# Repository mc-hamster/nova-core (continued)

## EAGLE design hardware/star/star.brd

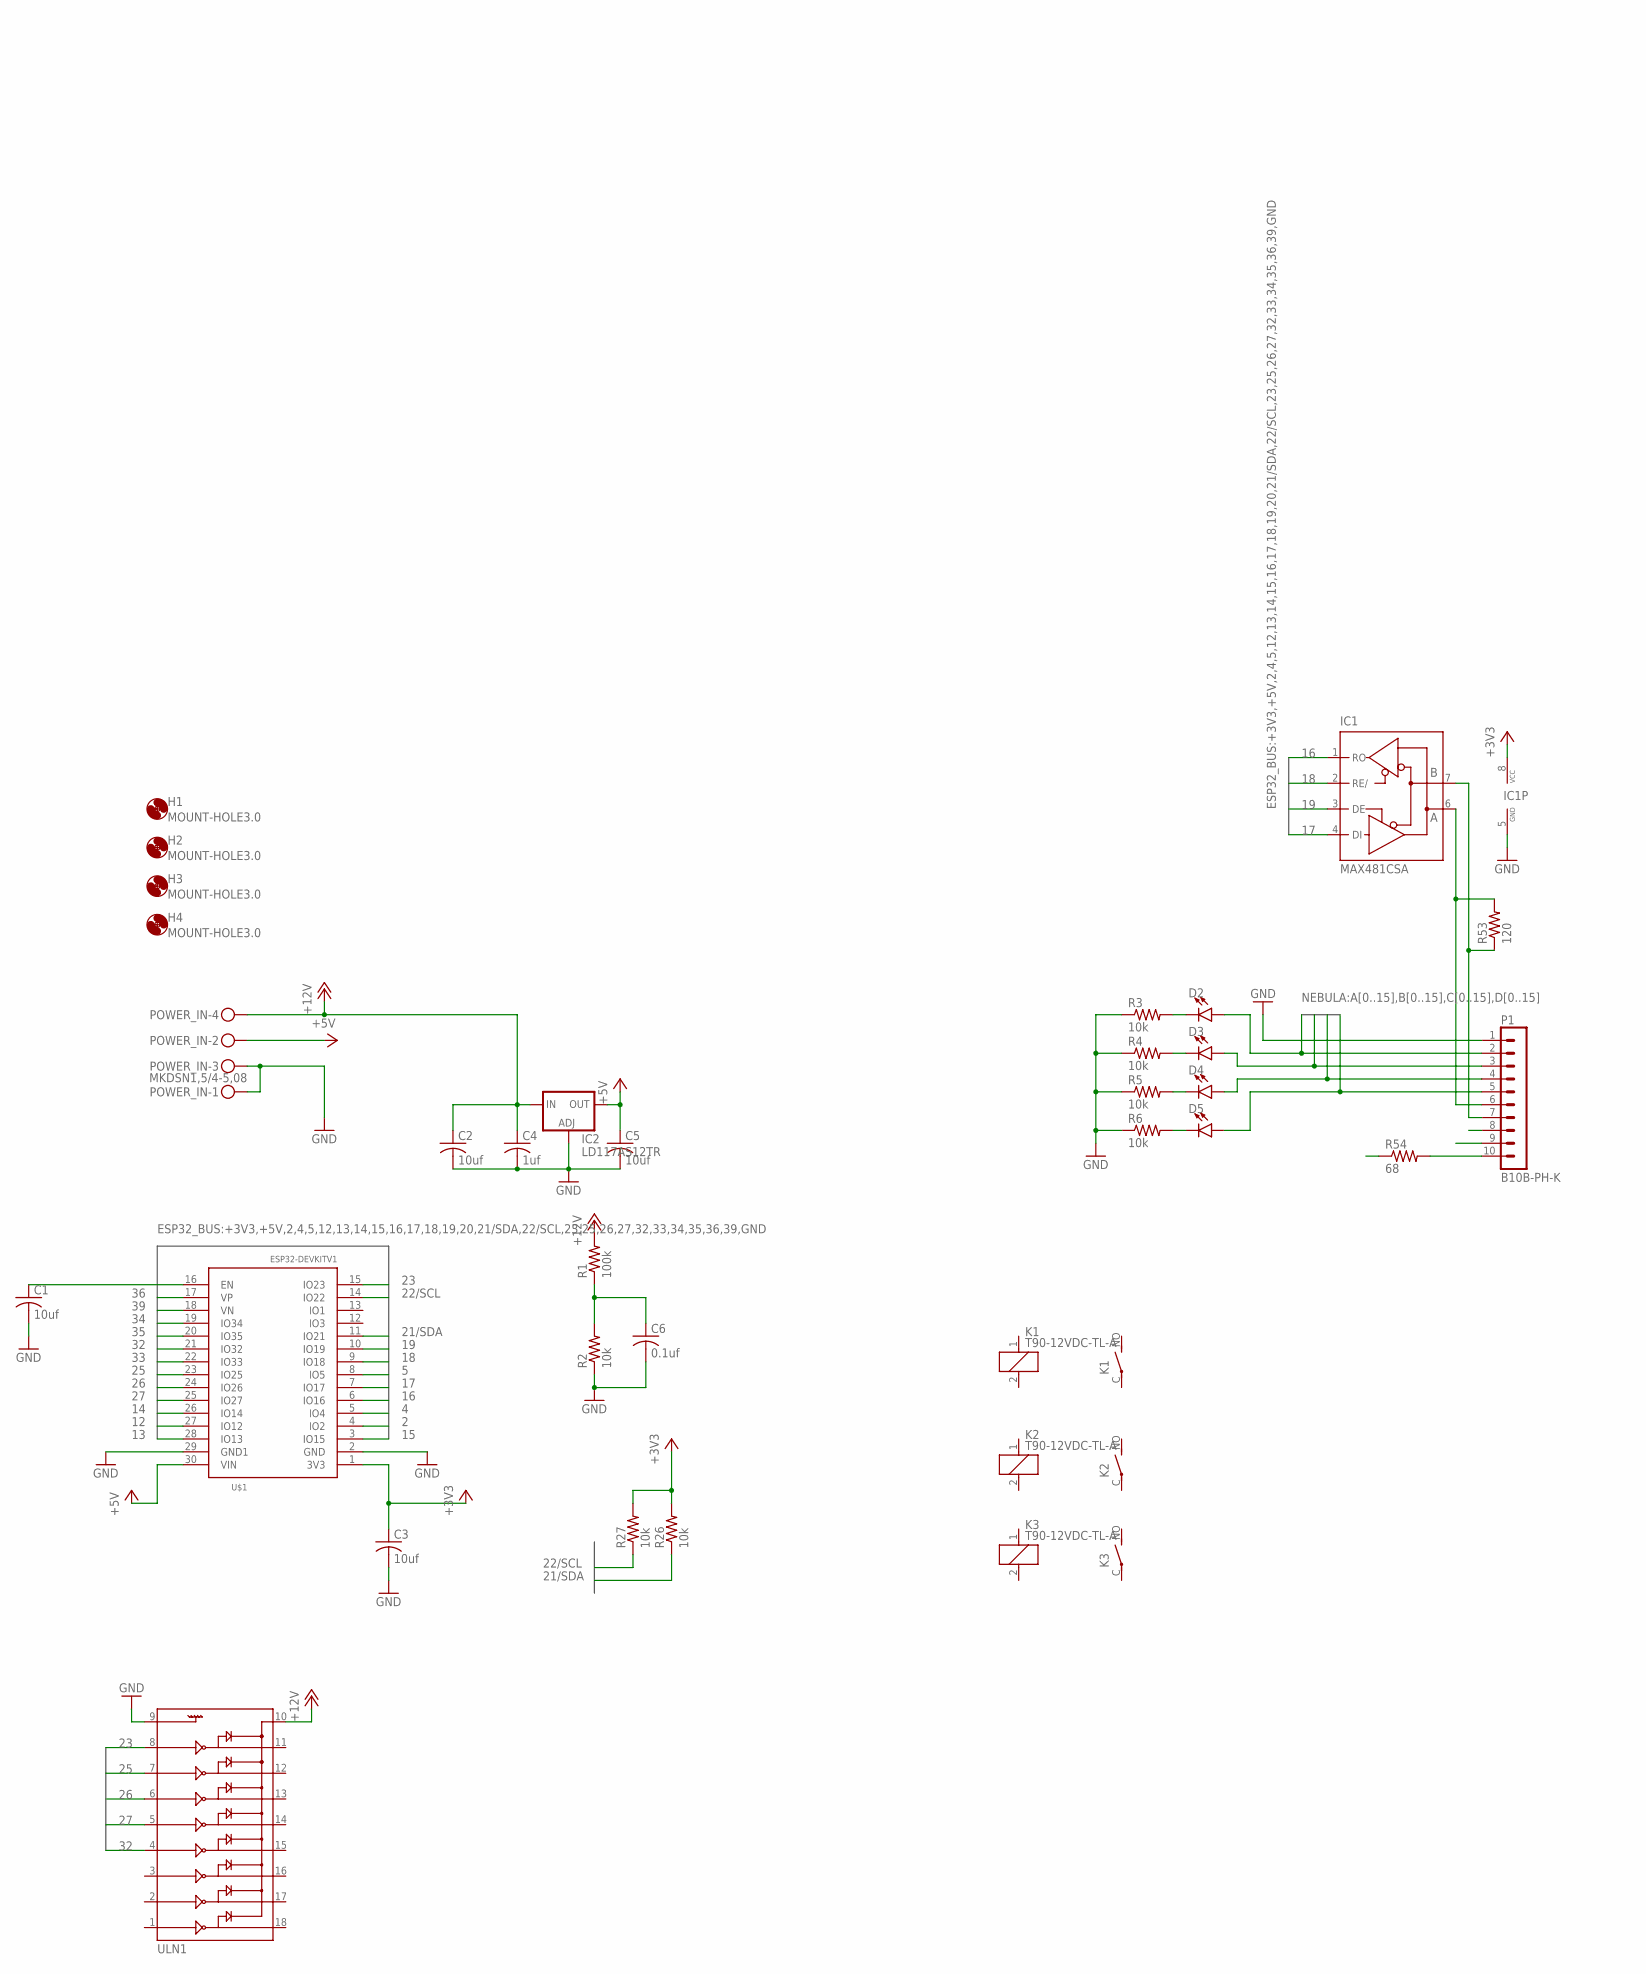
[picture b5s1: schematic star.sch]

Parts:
C1, C2, C3, C5: 10uf; C0603; LCSC_PART_NUMBER C19702
C4: 1uf; C0805; LCSC_PART_NUMBER C15849
C6: 0.1uf; C0603; LCSC_PART_NUMBER C14663
D2, D3, D4, D5: LED0603; LED-0603
H1, H2, H3, H4: MOUNT-HOLE3.0; 3,0
IC1: MAX481CSA; SO08
IC2: LD117AS12TR; SOT223; LCSC_PART_NUMBER C6187
K1, K2, K3: T90-12VDC-TL-A; JT1A-PCB
P1: B10B-PH-K
POWER_IN: MKDSN1,5/4-5,08
R1: 100k; R0603; LCSC_PART_NUMBER C25803
R2, R3, R4, R5, R6, R26, R27: 10k; R0603; LCSC_PART_NUMBER C25804
R53: 120; R0603; LCSC_PART_NUMBER C25804
R54: 68; R0603; LCSC_PART_NUMBER C25804
U$1: ESP32DEVKITV1; ESP32-DEVKITV1
ULN1: ULN2803SOIC; SO018

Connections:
2: U$1.4 (IO2)
4: U$1.5 (IO4)
5: U$1.8 (IO5)
12: U$1.27 (IO12)
13: U$1.28 (IO13)
14: U$1.26 (IO14)
15: U$1.3 (IO15)
16: IC1.1 (RO), U$1.6 (IO16)
17: IC1.4 (DI), U$1.7 (IO17)
18: IC1.2 (RE/), U$1.9 (IO18)
19: IC1.3 (DE), U$1.10 (IO19)
21/SDA: R26.1, U$1.11 (IO21)
22/SCL: R27.1, U$1.14 (IO22)
23: U$1.15 (IO23), ULN1.8
25: U$1.23 (IO25), ULN1.7
26: U$1.24 (IO26), ULN1.6
27: U$1.25 (IO27), ULN1.5
32: U$1.21 (IO32), ULN1.4
33: U$1.22 (IO33)
34: U$1.19 (IO34)
35: U$1.20 (IO35)
36: U$1.17 (VP)
39: C6.1, R1.1, R2.2, U$1.18 (VN)
+3V3: C3.1, IC1.8 (VCC), R26.2, R27.2, U$1.1 (3V3)
+5V: C5.1, IC2.4 (OUT), POWER_IN.2, U$1.30 (VIN)
+12V: C2.1, C4.1, IC2.3 (IN), POWER_IN.4, R1.2, ULN1.10
A0: D2.A, P1.2
A1: D3.A, P1.3
A2: D4.A, P1.4
A3: D5.A, P1.5
GND: C1.2, C2.2, C3.2, C4.2, C5.2, C6.2, IC1.5 (GND), IC2.1 (ADJ), P1.1, POWER_IN.1, POWER_IN.3, R2.1, R3.1, R4.1, R5.1, R6.1, U$1.2 (GND), U$1.29 (GND1), ULN1.9
unnamed: C1.1, U$1.16 (EN)
unnamed: D2.C, R3.2
unnamed: D3.C, R4.2
unnamed: D4.C, R5.2
unnamed: D5.C, R6.2
unnamed: P1.10, R54.2
unnamed: IC1.6 (A), P1.6, R53.2
unnamed: IC1.7 (B), P1.7, R53.1

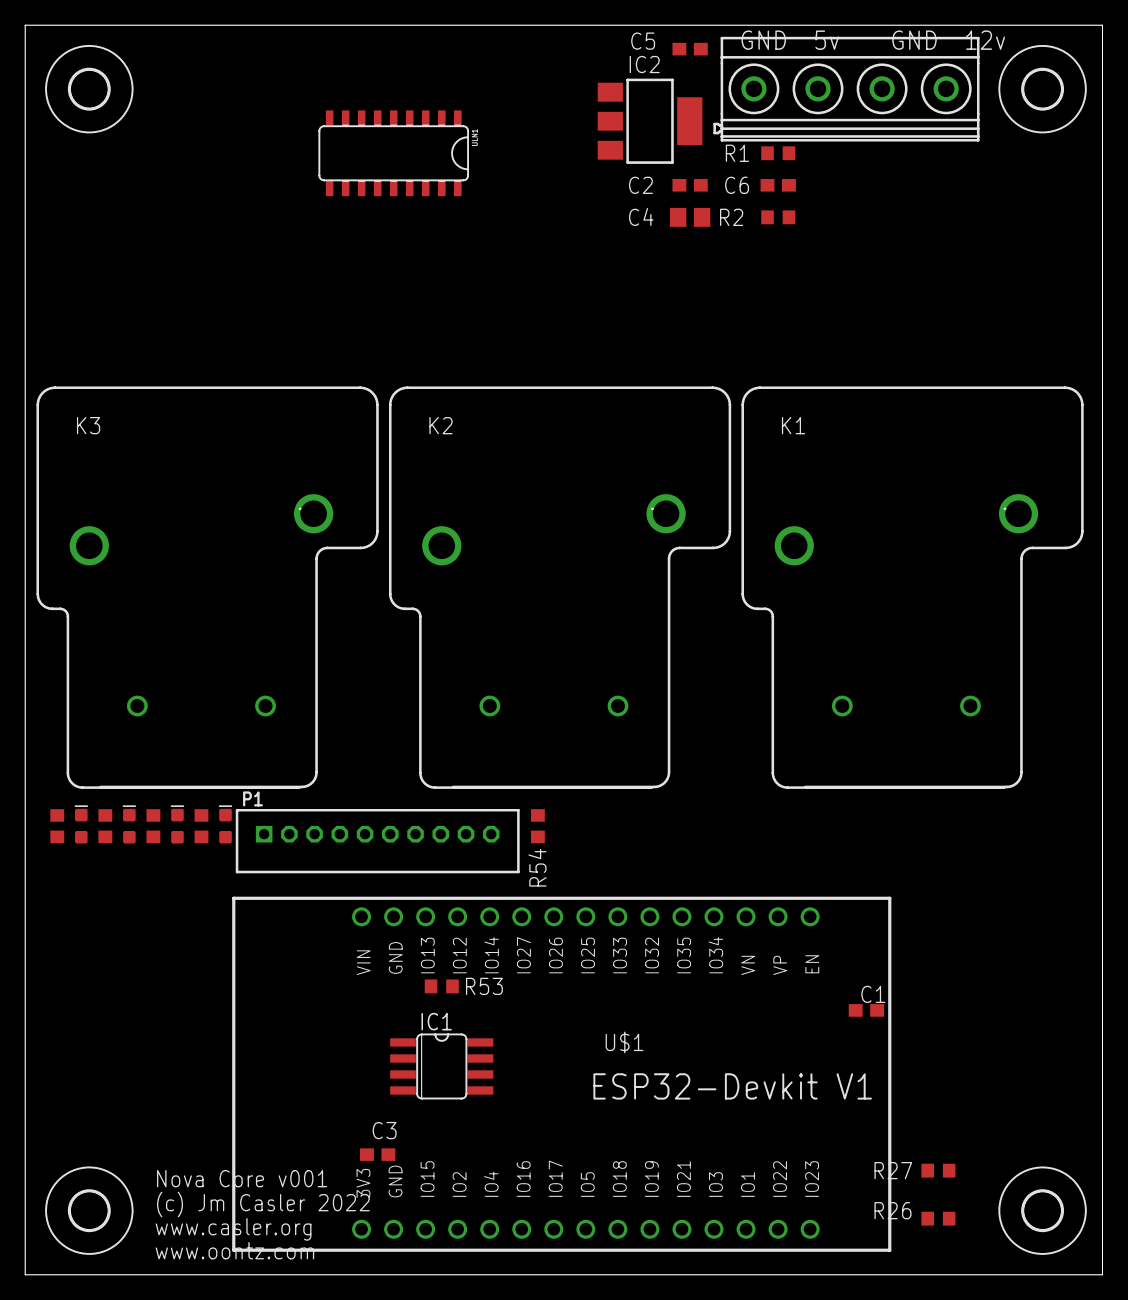
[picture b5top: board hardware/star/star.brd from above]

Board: 4 copper layers, 85.4 x 99.0 mm, 33 parts (0 on the bottom side), 28 nets.

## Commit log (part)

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2022-10-07 Initial checkin
2022-10-07 update schematic
2022-10-11 Core 001 Complete
2022-10-21 build out
2022-10-21 add async webserver example
2022-10-27 add MCP23X17 lib and code
2022-11-27 Nova 3.0 in progress. Needs line drivers.
2022-12-08 start of adding ULN to the outputs
2022-12-16 More Progress
2022-12-19 Completed v3
2022-12-23 Nova Core v3 - Sent to JLC PCB
2023-01-04 Fix for button status resistors & 12v status dim
    Fix for button status resistors & 12v status dim
2023-01-04 updated version number
2023-01-04 updated sample code using adafruit library
2023-01-21 Fixes interrupt on the "H" expander
2023-01-21 Initial work on class for read/write on gpio expander.
2023-01-21 Update boards to remove interrupt for all but expansion H
    Update boards to remove interrupt for all but expansion H
2023-01-22 Switch to FreeRTOS and using semaphores
2023-01-22 wrapper around writeGPIOAB to make it thread safe
2023-01-28 Added poofers, tank manifold and primary fuel shutoff.
2023-02-01 Update phoenix connectors & add JLC_ROTATION
2023-02-01 Replaced output resistor with 68 ohm (part c27592)
2023-02-02 espansion ports
2023-02-16 Add TVS and change led resistors to 1k
2023-02-16 misc board updates
2023-02-16 add midi v1.1 specification
2023-02-17 manual routing complete
2023-02-17 routed
2023-02-18 Updated labels
2023-02-24 v04 complete
2023-03-28 New methods to control button lights and emergenecy stop
2023-04-09 Add labels 5v and 3v3
2023-04-09 Rename src/Simona.cpp to src/modes/Simona.cpp
2023-04-09 Rename src/Simona.h to src/modes/Simona.h
2023-04-09 define output devices, first a star
2023-04-11 Abstract the digitalWrite methods to make them threadsafe
2023-04-11 buttons setup to have click, double and long press
2023-04-11 add more delay. this will give priority to other tasks
2023-04-12 buttons work to control the poofer
2023-04-16 multi-poof almost works
2023-04-21 Fix bug with stop getting in the way of the button lights
2023-04-22 start of boomer and longer running multi poofer
2023-04-25 it all works! fugly as heck but it works.
2023-04-25 add more output to serial console to help debugging
2023-04-25 cleanup serial console
2023-04-28 When button is pushed, blink the light associated with the button.
2023-05-04 New abstraction for port expanders. Use for go poof
2023-05-04 Fix watchdog timeout on system disable
2023-05-04 Set exhaust of boom to 4000ms
2023-05-05 Remap outputs for unscruz.
    I need to fix the cable pigtails. FMYL!
2023-05-06 Reduce button push timeout
2023-05-14 add esp32-s3
    (for future use)
2023-05-17 Reduce duration of poofer output
2023-05-17 Operate loops with smaller timings
2023-05-30 Tighter timing.
2023-05-30 Update loop delays in button thread
    This will improve UE when system is enabled and give priority to other threads when the system is disabled.
2023-05-30 Begin the use of jtag
2023-05-30 Task Ambient is now Task Enable
2023-05-30 Describe the class
2023-06-04 Move ESPUI to web
2023-06-04 Add ESPUI and ASyncTCP
2023-06-04 Improve responsiveness
2023-06-04 persistance to json
2023-06-15 add proto for the messaging request/response
2023-06-15 web interface
2023-06-19 no compile errors!
2023-06-19 fix compiler warning
2023-06-19 adding ReqRes. May end up removing this
2023-06-20 remove ReqRes
2023-06-20 make novaio easier to read
2023-06-30 Messages are now sent over the serial interface!
2023-07-02 stashing the v2 board with the new processor. likely not going to be used.
2023-07-02 re & de status LEDs added
2023-07-02 add definitions for the remaining outputs
2023-07-05 Add yields to Ambient
2023-07-07 Datasheet for the rs485 transceiver we use
2023-07-07 make crc16_ccitt easier to read
2023-07-07 monitor stack
2023-07-07 add mcp_h.pinMode
2023-07-07 Initial check in of LightUtils.
2023-07-08 Web interface controls lighting
2023-07-09 Control of lights over web interface works
2023-07-13 I2C clock to 400k & append mac to wifi AP
2023-07-13 add resetConfigSwitch and resetRebootSwitch
2023-07-13 Move xBlockTime to a precompiler define
2023-07-13 frames are being transmitted
2023-07-18 Fixed mapping of light fixgtures to the outputs.
2023-07-18 Continue program operation when returning
2023-07-18 Add the white_dot
2023-07-18 Refactor memory allocations
2023-07-18 Add whitedot and the other colors
2023-07-18 Reduce stack space and modify how often tasks run
2023-07-18 remove digitalWrite, it's not used and dangerous
2023-07-18 New "manual" tab
2023-07-18 cleanup and rename pooferInterval to pooferDuration
2023-07-19 Tune the tasks
2023-07-20 More tuning of the tasks
2023-07-20 Game works with the poofers!
2023-07-20 Clarified which frame average is reported
2023-07-20 Beginning of Boom sequences
    Beginning of Boom sequences
2023-07-23 Fix Pre & Post DMX mapping
2023-07-23 decrease frequency of free stack size reporting
2023-07-23 MVP! MVP! MVP!
2023-07-23 cleanup print statements in task loops
2023-07-24 Fix typo
2023-07-24 I think this done enough
2023-07-24 add documentation
2023-07-27 complete work on fog machines
2023-07-27 send Amnesia more reliably
2023-08-05 Exception decoded, copied from meshtastic
2023-08-05 automatic sequences
2023-08-05 add active feedback on button pushes
2023-08-06 add 500ms more fuel
2023-08-10 speed up brightness fade
2023-08-10 Remove settings tab
2023-08-12 Fix bug in init of bug 13->20
2023-08-12 New StarSequence library
2023-08-18 forgot to check this in
2023-08-27 3 more seconds of exhaust
2023-08-27 Simplify the game
2023-09-03 skip boom on star 6 (zero indexed)
2024-12-27 Update platformio.ini
    Updated to new espressif32 and littlefs
2025-03-02 combine nova star and nova core
2025-03-02 Remove unused variables.
2025-03-06 remove unused modes
2025-03-06 update comment
2025-03-06 reduce cpu load
2025-03-07 move buttons into modes
2025-03-07 initial integration of simona
2025-03-09 Upgrade libraries
2025-03-09 Simona is now fully ported to Nova
2025-03-09 Fix configurations
2025-03-09 Update colors
2025-03-10 Tidy up the console
2025-03-10 Clean up race condition
2025-03-10 Remove TaskButtons
2025-03-10 Remove task buttons
2025-03-10 fix web server heap crash
2025-03-10 The start of virtual stars
2025-03-10 make mutex a little safer
2025-03-10 Cache expansionDigitalRead reads to free up i2c bus
2025-03-10 Add i2c bus utilization
2025-03-11 Fix brightness not loading at startup
2025-03-12 task monitor
2025-03-12 first pass at novanow
2025-03-12 fix bug in rmt
2025-03-13 Update led <-> star <-> dmx map
2025-03-13 reverse second row
2025-03-13 "circular" mode
2025-03-13 added animations
2025-03-14 led animation porting complete
2025-03-14 change max rounds to 12
2025-03-15 reduce button flashing
2025-03-15 better but still broken
2025-03-16 shortened the music
2025-03-16 fixed random number generator
2025-03-16 comment out the goPoof serial print
2025-03-16 boomers are integrated
2025-03-16 suspend gametask and novanow on emergency
2025-03-16 add win animation
2025-03-16 fix prefernce name space error
2025-03-16 Refactoring to make it easier to read
2025-03-16 Revert "Refactoring to make it easier to read"
    This reverts commit 1a2426aa00bba131db1edb5a4b0cce5537a63259.
2025-03-17 Improve performance of TaskStars
2025-03-17 Config for disable debug messages in stars.cpp
2025-03-17 upgrade libs
2025-03-17 update blower off
2025-03-17 add yield
2025-03-17 fix local echo
2025-03-17 fix timing of stars
2025-03-17 wifimulti
2025-03-18 Revert "Fix stalled tasks"
    This reverts commit 07517c7216bb89cdf079c6cdaf90f9eb23ba0c11.
2025-03-18 Revert "Create wifi_config.h"
    This reverts commit 89ce5e07fefa8dec5ebfdf949daa17e2fff7a561.
2025-03-19 fix compiler errors
2025-03-19 fix stalling condition (non critical)
2025-03-19 Update monitoring
2025-03-19 Fix formatting and add startup music
2025-03-20 Update protocol with fogEnabled
2025-03-20 Revert "Update Tasks.cpp"
    This reverts commit a6069fd257d096d91a2489869f4efc050a34c41c.
2025-03-20 update star with fog enable proto
2025-03-20 Refactor NovaNet, NovaIO and FogMachine
2025-03-21 Remove all star, add fogEnabled
2025-03-21 Fix STA status bug, start to add Fog control
2025-03-21 remove fake circular lighting
2025-03-21 fix brightness on startup
2025-03-21 remove mdns
2025-03-21 remove captive portal
2025-03-21 stability improvements
2025-03-22 debouncing
2025-03-22 Updated libs
2025-03-25 Emergency = Turn off Fog Machines
2025-03-26 pass fog messages
2025-03-26 end point works! not yet tested
2025-03-26 update sequences
2025-03-31 add screen and endpoin
2025-04-01 Updates to screen
2025-04-08 Fix xSemaphoreTake bug in NovaIO
2025-04-08 bump priority to 3
2025-04-08 reformat
2025-04-10 Add more loggint to IO
2025-04-10 Switch to case statement
2025-04-10 Bump I2C speed
2025-04-10 i2c reporting
2025-04-23 begin implementation of sensors on nova star
2025-06-09 Fix crash on web update. Caused by update status message
2025-06-10 wrap midi messages in mutex
2025-07-19 Removed web loop mutex
2025-07-19 lightutils format
2025-07-19 Increase amnesia interval and add debug logging
    Changed amnesia trigger interval from 1s to 2s. Improved fogEnabled logic formatting and added debug output for fogEnabled status in runAmnesiaCode.
2025-07-19 Add full sequence display for Simona game
    Introduces methods in Simona to retrieve and format the full LED sequence, exposes it via the web interface, and adds a new label to display the sequence in the UI. Also refines fog control panel lab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
2025-07-19 Fix label for fog output max time slider
    Corrects the label from 'Min' to 'Max' for the fog output max time slider control in the web setup, ensuring proper UI representation.
2025-07-20 Increase loop execution interval to 30 seconds
    Changed the interval for executing the average frame time calculation in Ambient::loop from 10 seconds to 30 seconds to reduce frequency of this operation.
2025-07-20 Add debug prints for input collection stage
    Added Serial print statements to log entry into SIMONA_STAGE_INPUT_COLLECTION and button presses, aiding in debugging input handling.
2025-07-27 Add BOOM_IGNITE_PIN monitoring and min/max Z accel tracking
    Introduces BOOM_IGNITE_PIN definition and initialization, and updates the Sensors task to monitor the pin. When triggered, the system records min/max Z acceleration values and sample count over a 1-s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
2025-07-29 Update TelemetryResponse fields and fix enum typo
    Renamed REQUEST_ELEMETRY to REQUEST_TELEMETRY in the RequestType enum. Replaced the peak_boom field in TelemetryResponse with accel_min_z, accel_max_z, accel_min_z_time, and accel_max_z_time fields, 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
2025-07-29 Update TelemetryResponse fields and fix enum typo
    Replaces 'peak_boom' with acceleration and timing fields in messaging_TelemetryResponse, adds 'sketch_compile_time', and updates related macros and initializers. Also corrects a typo in the RequestTy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
2025-07-29 Refactor RS485 control and request handling logic
    Replaces setStarlink's direction argument with a StarlinkDirection enum for clarity and safety, and updates its implementation. Refactors NovaNet request payload handling to use a switch statement fo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
2025-07-30 Refactor star network output and add netIn function
    Refactored the netOut function for clarity and efficiency, ensuring only necessary writes are performed. Added a new netIn function to set a selected star to receive mode while setting others to high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
2025-07-30 Add periodic telemetry request to Ambient
    Introduces a requestTelemetry method in Ambient to send telemetry requests to each star every 30 seconds. Updates the loop to call this new method and exposes it in the header file.
2025-08-01 Add NovaArt WiFi network to configuration
    Included a new WiFi network entry for 'NovaArt' with its corresponding password in the networks array.
2025-08-22 Update DMX pin setup and adjust sensor task initialization
    Set DMX hardware pins in DmxNet constructor and ensure DMX packets are sent after writing data. Commented out sensor initialization and related task creation in main.cpp, likely for debugging or to t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
